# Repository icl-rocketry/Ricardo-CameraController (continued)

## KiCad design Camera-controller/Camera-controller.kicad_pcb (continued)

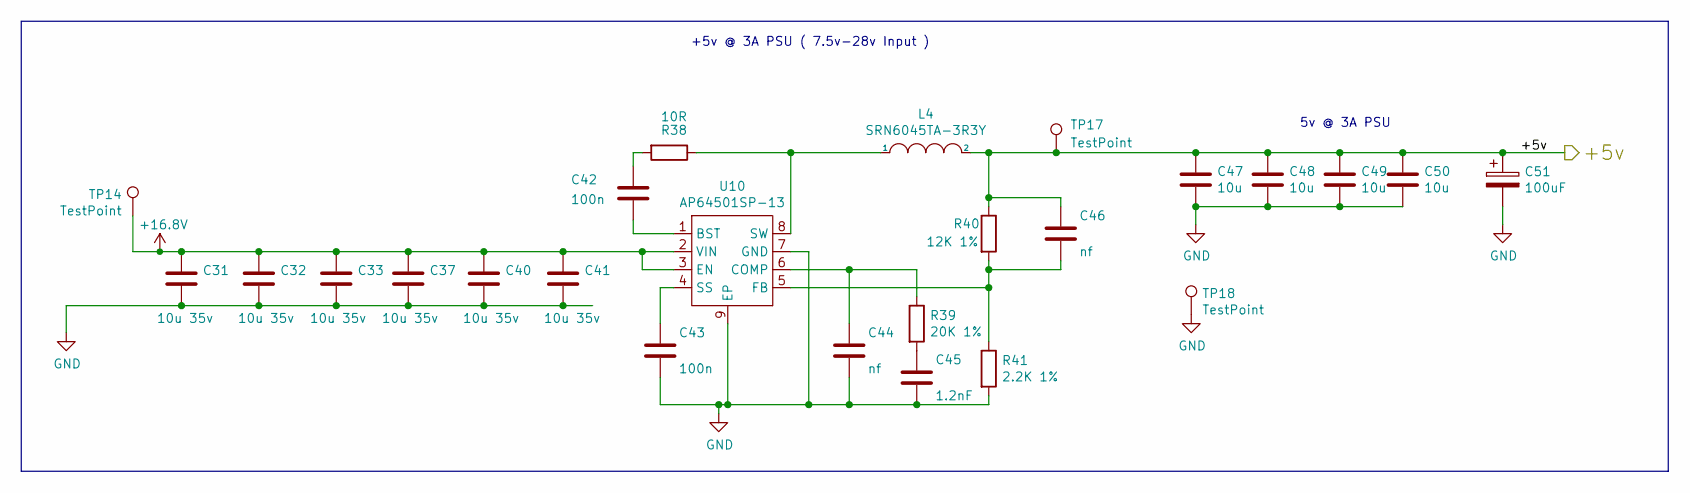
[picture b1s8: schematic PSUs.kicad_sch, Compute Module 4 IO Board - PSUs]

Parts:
C31, C32, C33, C37, C40, C41: 10u 35v; C_0805_2012Metric; Part Description 10uF 10% or 20% 35V Ceramic Capacitor X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
C42, C43: 100n; C_0402_1005Metric; Part Description 0.1uF 10% 16V Ceramic Capacitor X7R 040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
C44: nf; C_0402_1005Metric
C45: 1.2nF; C_0402_1005Metric; Part Description 1200pF 10% 10V Ceramic Capacitor X5R 04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
C46: nf; C_0402_1005Metric; Part Description 220 pF, 50 V, 0402 [1005 Metric], ± 5%,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
C47, C48, C49, C50: 10u; C_0805_2012Metric; Part Description 10uF 10% 10V Ceramic Capacitor X7R 0805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
C51: 100uF; CP_EIA-7343-31_Kemet-D; Part Description Capacitor, SP-Cap, 100u, 6.3V, 15mR ESR
L4: SRN6045TA-3R3Y; L_Bourns_SRN6045TA; Part Description 3.3µH Semi-Shielded Wirewound Inductor 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
R38: 10R; R_0402_1005Metric; Part Description Resistor 10R M1005 1% 63mW
R39: 20K 1%; R_0402_1005Metric; Part Description Resistor 20K M1005 1% 63mW
R40: 12K 1%; R_0402_1005Metric; Part Description Resistor 12K M1005 1% 63mW
R41: 2.2K 1%; R_0402_1005Metric; Part Description Resistor 2.2K M1005 1% 63mW
TP14, TP17, TP18: TestPoint; TestPoint_Pad_2.0x2.0mm
U10: AP64501SP-13; SOIC-8-1EP_3.9x4.9mm_P1.27mm_EP2.95x4.9mm_Mask2.71x3.4mm_Th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; Part Description Buck Switching Regulator IC Positive Ad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

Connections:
unnamed: C42.1, R38.2
unnamed: C45.1, R39.2
unnamed: C42.2, U10.1 (BST)
unnamed 188: C44.1, R39.1, U10.6 (COMP); also elsewhere on the board
unnamed: C43.1, U10.4 (SS)

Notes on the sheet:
5v @ 3A PSU
+5v @ 3A PSU ( 7.5v-28v Input )

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
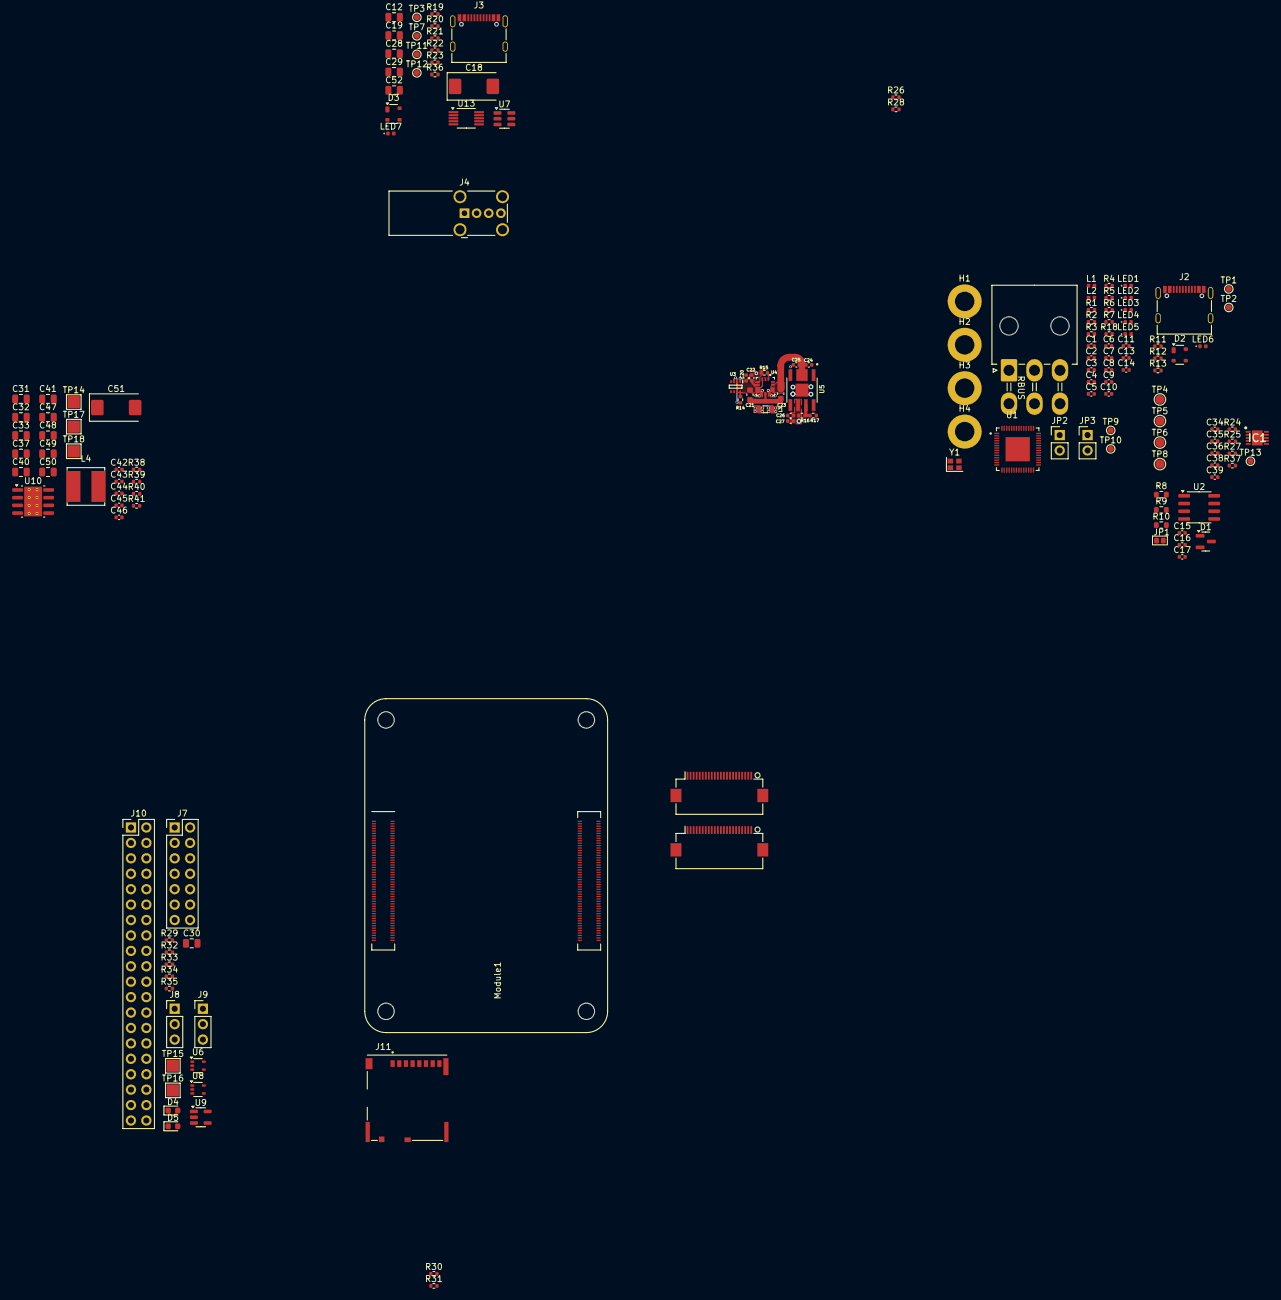
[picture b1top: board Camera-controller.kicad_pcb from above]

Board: 4 copper layers, 159 parts (0 on the bottom side), 141 nets.

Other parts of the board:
C15: 100nF; C_0402_1005Metric
C16: 10uF; C_0402_1005Metric
C17: 47nF; C_0402_1005Metric
D1: SM712_SOT23; SOT-23
JP1: TermJP; SmallerSolderJP
R8: 0; R_0603_1608Metric
R9, R10: 60; R_0603_1608Metric
U2: SN65HVD230; SOIC-8_3.9x4.9mm_P1.27mm

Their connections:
+3V3: C15.1, C16.1, U2.3 (VCC); also elsewhere on the board
/CAN+: D1.2 (A2), R9.1, U2.7 (CANH); also elsewhere on the board
/CAN-: D1.1 (A1), R10.2, U2.6 (CANL); also elsewhere on the board
/CAN-BUS/Vref: JP1.1 (A), U2.5 (Vref)
/CAN_RX: U2.4 (R); also elsewhere on the board
/CAN_TX: U2.1 (D); also elsewhere on the board
unnamed: C17.1, JP1.2 (B), R9.2, R10.1
unnamed: R8.1, U2.8 (Rs)

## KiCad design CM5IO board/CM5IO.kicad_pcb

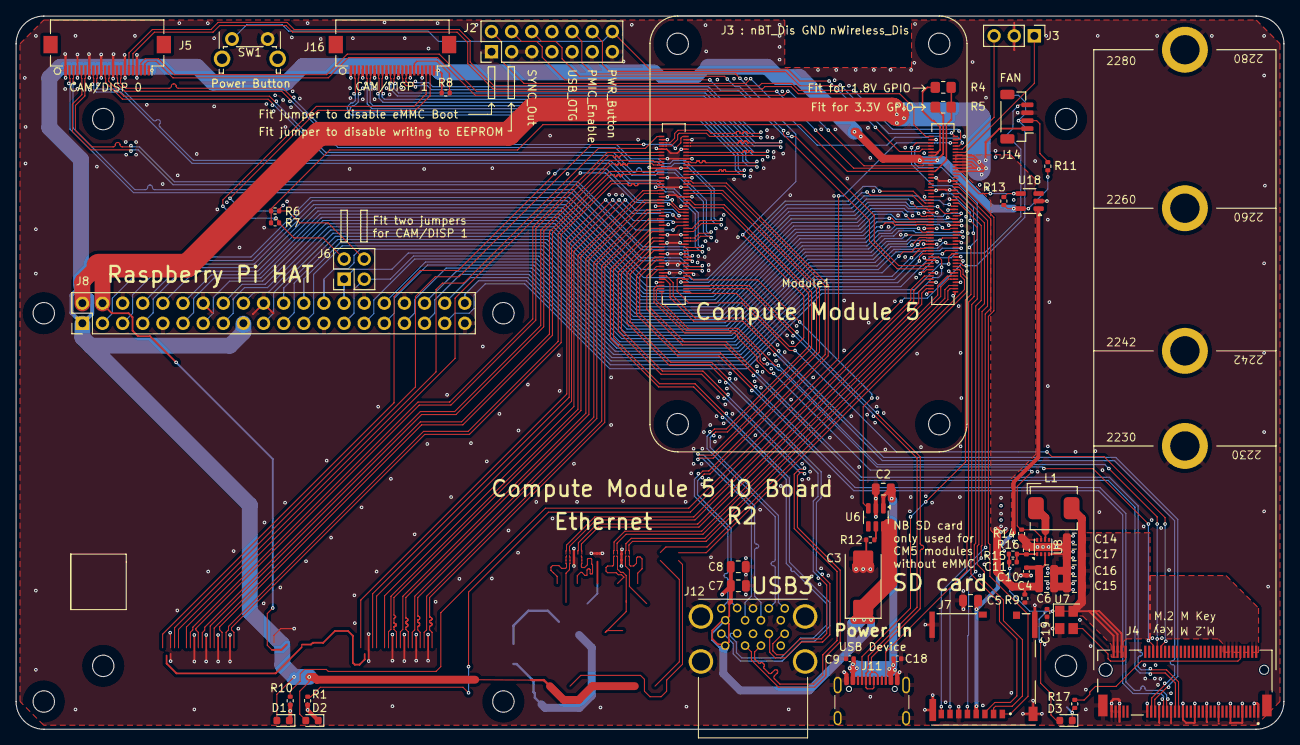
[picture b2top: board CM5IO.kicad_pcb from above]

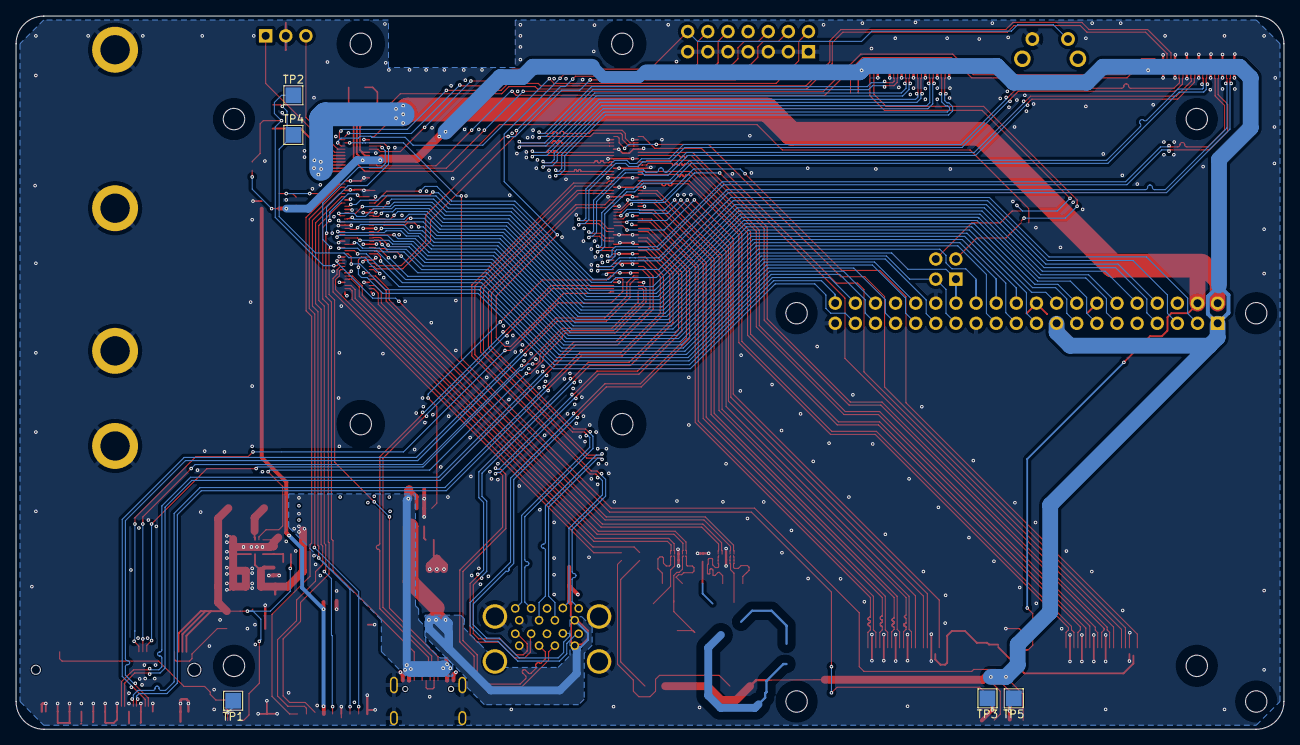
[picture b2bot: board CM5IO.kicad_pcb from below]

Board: 4 copper layers, 160.0 x 90.0 mm, 65 parts (5 on the bottom side), 118 nets.

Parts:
C2, C4, C5, C6, C7, C8, C14, C15, C16, C17: 10u; C_0805_2012Metric
C3: 100uF; CP_EIA-7343-31_Kemet-D
C9, C10, C18, C19: 100n; C_0402_1005Metric
C11: 4.7nF; C_0402_1005Metric
D1: LED Red; LED_0603_1608Metric
D2, D3: LED Green; LED_0603_1608Metric
H1, H2, H3, H4, H5, H6, H7, H8: MountingHole; MountingHole_2.7mm_M2.5_DIN965
J2: Conn_02x07_Odd_Even; PinHeader_2x07_P2.54mm_Vertical
J3: Conn_01x03; PinHeader_1x03_P2.54mm_Vertical
J4: Bus_M.2_Socket_M; M.2 M Key socket
J5, J16: Conn_01x22_Female; Hirose_FH12-22S-0.5SH_1x22-1MP_P0.50mm_Horizontal
J6: THD-02-R; PinHeader_2x02_P2.54mm_Vertical
J7: Micro_SD_Card_Det; SDCARD_MOLEX_503398-1892
J8: THD-20-R; PinHeader_2x20_P2.54mm_Vertical
J11: USB_C_Receptacle_USB2.0; USB_C_Receptacle_GCT_USB4105-xx-A_16P_TopMnt_Horizontal
J12: USB3_A; MTCONN_UBAF30-D2011
J14: JST_SHBM04B-SRSS-TB; JST_SH_BM04B-SRSS-TB_1x04-1MP_P1.00mm_Vertical
L1: 2.2uH; L_Bourns_SRP5030CC
Module1: ComputeModule5-CM5; Raspberry-Pi-5-Compute-Module
R1, R10, R17: 1k; R_0402_1005Metric
R4: nf; R_0805_2012Metric_Pad1.20x1.40mm_HandSolder
R5: 0R; R_0805_2012Metric_Pad1.20x1.40mm_HandSolder
R6, R7, R8, R9, R16: 2.2K 1%; R_0402_1005Metric
R11, R13, R15: 10K 1%; R_0402_1005Metric
R12: 15K 1%; R_0402_1005Metric
R14: 100K 1%; R_0402_1005Metric
SW1: Right angle Tact button; SW_Tactile_SPST_Angled_PTS645Vx58-2LFS
TP1, TP2, TP3, TP4, TP5: TestPoint; TestPoint_Pad_2.0x2.0mm
U6: AP22653W6; SOT-23-6
U7: ASEK-32.768KHZ-L-R-T; Crystal_SMD_3225-4Pin_3.2x2.5mm
U8: AP3441SHE-7B; DFN-8-1EP_2x2mm_P0.5mm_EP1.05x1.75mm
U18: RT9742GGJ5; SOT-23-5

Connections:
/+3.3v: D1.2 (A), D2.2 (A), J5.22, J8.1, J8.17, J16.22, Module1.84 (+3.3v_(Output)), Module1.86 (+3.3v_(Output)), R5.1, R8.1, R11.1, R13.1, U18.5 (IN)
/+5v: C4.1, C6.1, C9.1, C10.1, C18.1, J8.2, J8.4, J11.A4 (VBUS), J11.A9 (VBUS), J11.B4 (VBUS), J11.B9 (VBUS), J14.1, Module1.77 (+5v_(Input)), Module1.79 (+5v_(Input)), Module1.81 (+5v_(Input)), Module1.83 (+5v_(Input)), Module1.85 (+5v_(Input)), Module1.87 (+5v_(Input)), R9.1, U8.3 (VIN)
/CC1: J11.A5 (CC1), Module1.94 (CC1)
/CC2: J11.B5 (CC2), Module1.96 (CC2)
/CM5_GPIO ( Ethernet, GPIO, SDCARD)/+1.8v: Module1.88 (+1.8v_(Output)), Module1.90 (+1.8v_(Output)), R4.1
/CM5_GPIO ( Ethernet, GPIO, SDCARD)/BT_nDis: J3.3, Module1.91 (BT_nDisable)
/CM5_GPIO ( Ethernet, GPIO, SDCARD)/CAM_GPIO0: J5.17, Module1.97 (CAM_GPIO0)
/CM5_GPIO ( Ethernet, GPIO, SDCARD)/CAM_GPIO1: J5.18, Module1.100 (CAM_GPIO1)
/CM5_GPIO ( Ethernet, GPIO, SDCARD)/EEPROM_nWP: J2.4, Module1.20 (EEPROM_nWP)
/CM5_GPIO ( Ethernet, GPIO, SDCARD)/GPIO2: J8.3, Module1.58 (GPIO2)
/CM5_GPIO ( Ethernet, GPIO, SDCARD)/GPIO3: J8.5, Module1.56 (GPIO3)
/CM5_GPIO ( Ethernet, GPIO, SDCARD)/GPIO4: J8.7, Module1.54 (GPIO4)
/CM5_GPIO ( Ethernet, GPIO, SDCARD)/GPIO5: J8.29, Module1.34 (GPIO5)
/CM5_GPIO ( Ethernet, GPIO, SDCARD)/GPIO6: J8.31, Module1.30 (GPIO6)
/CM5_GPIO ( Ethernet, GPIO, SDCARD)/GPIO7: J8.26, Module1.37 (GPIO7)
/CM5_GPIO ( Ethernet, GPIO, SDCARD)/GPIO8: J8.24, Module1.39 (GPIO8)
/CM5_GPIO ( Ethernet, GPIO, SDCARD)/GPIO9: J8.21, Module1.40 (GPIO9)
/CM5_GPIO ( Ethernet, GPIO, SDCARD)/GPIO10: J8.19, Module1.44 (GPIO10)
/CM5_GPIO ( Ethernet, GPIO, SDCARD)/GPIO11: J8.23, Module1.38 (GPIO11)
/CM5_GPIO ( Ethernet, GPIO, SDCARD)/GPIO12: J8.32, Module1.31 (GPIO12)
/CM5_GPIO ( Ethernet, GPIO, SDCARD)/GPIO13: J8.33, Module1.28 (GPIO13)
/CM5_GPIO ( Ethernet, GPIO, SDCARD)/GPIO14: J8.8, Module1.55 (GPIO14)
/CM5_GPIO ( Ethernet, GPIO, SDCARD)/GPIO15: J8.10, Module1.51 (GPIO15)
/CM5_GPIO ( Ethernet, GPIO, SDCARD)/GPIO16: J8.36, Module1.29 (GPIO16)
/CM5_GPIO ( Ethernet, GPIO, SDCARD)/GPIO17: J8.11, Module1.50 (GPIO17)
/CM5_GPIO ( Ethernet, GPIO, SDCARD)/GPIO18: J8.12, Module1.49 (GPIO18)
/CM5_GPIO ( Ethernet, GPIO, SDCARD)/GPIO19: J8.35, Module1.26 (GPIO19)
/CM5_GPIO ( Ethernet, GPIO, SDCARD)/GPIO20: J8.38, Module1.27 (GPIO20)
/CM5_GPIO ( Ethernet, GPIO, SDCARD)/GPIO21: J8.40, Module1.25 (GPIO21)
/CM5_GPIO ( Ethernet, GPIO, SDCARD)/GPIO22: J8.15, Module1.46 (GPIO22)
/CM5_GPIO ( Ethernet, GPIO, SDCARD)/GPIO23: J8.16, Module1.47 (GPIO23)
/CM5_GPIO ( Ethernet, GPIO, SDCARD)/GPIO24: J8.18, Module1.45 (GPIO24)
/CM5_GPIO ( Ethernet, GPIO, SDCARD)/GPIO25: J8.22, Module1.41 (GPIO25)
/CM5_GPIO ( Ethernet, GPIO, SDCARD)/GPIO26: J8.37, Module1.24 (GPIO26)
/CM5_GPIO ( Ethernet, GPIO, SDCARD)/GPIO27: J8.13, Module1.48 (GPIO27)
/CM5_GPIO ( Ethernet, GPIO, SDCARD)/GPIO_VREF: Module1.78 (GPIO_VREF(1.8v/3.3v_Input)), R4.2, R5.2, R6.1, R7.1
/CM5_GPIO ( Ethernet, GPIO, SDCARD)/ID_SC: J6.1, J8.28, Module1.35 (ID_SC)
/CM5_GPIO ( Ethernet, GPIO, SDCARD)/ID_SD: J6.3, J8.27, Module1.36 (ID_SD)
/CM5_GPIO ( Ethernet, GPIO, SDCARD)/PMIC_ENABLE: J2.12, Module1.99 (PMIC_ENABLE)
/CM5_GPIO ( Ethernet, GPIO, SDCARD)/PWM: J14.2, Module1.19 (FAN_PWM), R11.2, TP2.1
/CM5_GPIO ( Ethernet, GPIO, SDCARD)/PWR_BUT: J2.14, Module1.92 (PWR_BUT), SW1.1
/CM5_GPIO ( Ethernet, GPIO, SDCARD)/SD_CLK: J7.5 (CLK), Module1.57 (SD_CLK)
/CM5_GPIO ( Ethernet, GPIO, SDCARD)/SD_CMD: J7.3 (CMD), Module1.62 (SD_CMD)
/CM5_GPIO ( Ethernet, GPIO, SDCARD)/SD_DAT0: J7.7 (DAT0), Module1.63 (SD_DAT0)
/CM5_GPIO ( Ethernet, GPIO, SDCARD)/SD_DAT1: J7.8 (DAT1), Module1.67 (SD_DAT1)
/CM5_GPIO ( Ethernet, GPIO, SDCARD)/SD_DAT2: J7.1 (DAT2), Module1.69 (SD_DAT2)
/CM5_GPIO ( Ethernet, GPIO, SDCARD)/SD_DAT3: J7.2 (DAT3/CD), Module1.61 (SD_DAT3)
/CM5_GPIO ( Ethernet, GPIO, SDCARD)/SD_PWR: C5.1, J7.4 (VDD), U18.1 (OUT)
/CM5_GPIO ( Ethernet, GPIO, SDCARD)/SD_PWR_ON: Module1.75 (SD_PWR_ON), R13.2, U18.4 (EN)
/CM5_GPIO ( Ethernet, GPIO, SDCARD)/TACHO: J14.4, Module1.16 (FAN_TACHO), TP4.1
/CM5_GPIO ( Ethernet, GPIO, SDCARD)/USBOTG: J2.10, Module1.101 (USB_OTG_ID)
/CM5_GPIO ( Ethernet, GPIO, SDCARD)/WL_nDis: J3.1, Module1.89 (WiFi_nDisable)
/CM5_GPIO ( Ethernet, GPIO, SDCARD)/nPWR_LED: Module1.95 (LED_nPWR), R10.2
/CM5_GPIO ( Ethernet, GPIO, SDCARD)/nRPIBOOT: J2.2, Module1.93 (nRPIBOOT)
/CM5_HighSpeed/+5v: C2.1, U6.1 (IN)
/CM5_HighSpeed/DPHY0_C_N: J5.8, Module1.127 (MIPI0_C_N)
/CM5_HighSpeed/DPHY0_C_P: J5.9, Module1.129 (MIPI0_C_P)
/CM5_HighSpeed/DPHY0_D0_N: J5.2, Module1.115 (MIPI0_D0_N)
/CM5_HighSpeed/DPHY0_D0_P: J5.3, Module1.117 (MIPI0_D0_P)
/CM5_HighSpeed/DPHY0_D1_N: J5.5, Module1.121 (MIPI0_D1_N)
/CM5_HighSpeed/DPHY0_D1_P: J5.6, Module1.123 (MIPI0_D1_P)
/CM5_HighSpeed/DPHY0_D2_N: J5.11, Module1.133 (MIPI0_D2_N)
/CM5_HighSpeed/DPHY0_D2_P: J5.12, Module1.135 (MIPI0_D2_P)
/CM5_HighSpeed/DPHY0_D3_N: J5.14, Module1.139 (MIPI0_D3_N)
/CM5_HighSpeed/DPHY0_D3_P: J5.15, Module1.141 (MIPI0_D3_P)
/CM5_HighSpeed/DPHY1_C_N: J16.8, Module1.187 (MIPI1_C_N)
/CM5_HighSpeed/DPHY1_C_P: J16.9, Module1.189 (MIPI1_C_P)
/CM5_HighSpeed/DPHY1_D0_N: J16.2, Module1.175 (MIPI1_D0_N)
/CM5_HighSpeed/DPHY1_D0_P: J16.3, Module1.177 (MIPI1_D0_P)
/CM5_HighSpeed/DPHY1_D1_N: J16.5, Module1.181 (MIPI1_D1_N)
/CM5_HighSpeed/DPHY1_D1_P: J16.6, Module1.183 (MIPI1_D1_P)
/CM5_HighSpeed/DPHY1_D2_N: J16.11, Module1.193 (MIPI1_D2_N)
/CM5_HighSpeed/DPHY1_D2_P: J16.12, Module1.195 (MIPI1_D2_P)
/CM5_HighSpeed/DPHY1_D3_N: J16.14, Module1.194 (MIPI1_D3_N)
/CM5_HighSpeed/DPHY1_D3_P: J16.15, Module1.196 (MIPI1_D3_P)
/CM5_HighSpeed/PCIE_CLK_N: J4.53 (REFCLKn), Module1.112 (PCIe_CLK_N)
/CM5_HighSpeed/PCIE_CLK_P: J4.55 (REFCLKp), Module1.110 (PCIe_CLK_P)
/CM5_HighSpeed/PCIE_PWR_EN: Module1.106 (PCIE_PWR_EN), R14.1, U8.7 (EN)
/CM5_HighSpeed/PCIE_RX_N: J4.43 (PETp0), Module1.118 (PCIe_RX_N)
/CM5_HighSpeed/PCIE_RX_P: J4.41 (PETn0), Module1.116 (PCIe_RX_P)
/CM5_HighSpeed/PCIE_TX_N: J4.49 (PERp0), Module1.124 (PCIe_TX_N)
/CM5_HighSpeed/PCIE_TX_P: J4.47 (PERn0), Module1.122 (PCIe_TX_P)
/CM5_HighSpeed/PCIE_nCLKREQ: J4.52 (~CLKREQ), Module1.102 (PCIe_nCLKREQ)
/CM5_HighSpeed/PCIE_nRST: J4.50 (~PERST), Module1.109 (PCIe_nRST)
/CM5_HighSpeed/PCIE_nWAKE: J4.54 (~PEWAKE), Module1.104 (PCIE_nWAKE)
/CM5_HighSpeed/SCL0: J5.20, Module1.80 (SCL0)
/CM5_HighSpeed/SCL1: J6.2, J16.20, R7.2
/CM5_HighSpeed/SDA0: J5.21, Module1.82 (SDA0)
/CM5_HighSpeed/SDA1: J6.4, J16.21, R6.2
/CM5_HighSpeed/USB3-0-D_N: J12.A2 (D-), Module1.136 (USB3-0-D_N)
/CM5_HighSpeed/USB3-0-D_P: J12.A3 (D+), Module1.134 (USB3-0-D_P)
/CM5_HighSpeed/USB3-0-RX_N: J12.A6 (SSRX+), Module1.128 (USB3-0-RX_N)
/CM5_HighSpeed/USB3-0-RX_P: J12.A5 (SSRX-), Module1.130 (USB3-0-RX_P)
/CM5_HighSpeed/USB3-0-TX_N: J12.A9 (SSTX+), Module1.140 (USB3-0-TX_N)
/CM5_HighSpeed/USB3-0-TX_P: J12.A8 (SSTX-), Module1.142 (USB3-0-TX_P)
/CM5_HighSpeed/USB3-1-D_N: J12.B2 (D-), Module1.165 (USB3-1-D_N)
/CM5_HighSpeed/USB3-1-D_P: J12.B3 (D+), Module1.163 (USB3-1-D_P)
/CM5_HighSpeed/USB3-1-RX_N: J12.B6 (SSRX+), Module1.157 (USB3-1-RX_N)
/CM5_HighSpeed/USB3-1-RX_P: J12.B5 (SSRX-), Module1.159 (USB3-1-RX_P)
/CM5_HighSpeed/USB3-1-TX_N: J12.B9 (SSTX+), Module1.169 (USB3-1-TX_N)
/CM5_HighSpeed/USB3-1-TX_P: J12.B8 (SSTX-), Module1.171 (USB3-1-TX_P)
/CM5_HighSpeed/VBUS: C3.1, C7.1, C8.1, J12.A1 (VBUS), J12.B1 (VBUS), U6.6 (OUT)
/CM5_HighSpeed/VBUS_EN: Module1.111 (VBUS_EN), U6.3 (EN)
/PCIe-M2/FB: C11.2, R15.2, R16.1, U8.1 (FB)
/PCIe-M2/M2_3v3: C11.1, C14.1, C15.1, C16.1, C17.1, C19.1, D3.2 (A), J4.2 (3.3V), J4.4 (3.3V), J4.12 (3.3V), J4.14 (3.3V), J4.16 (3.3V), J4.18 (3.3V), J4.70 (3.3V), J4.72 (3.3V), J4.74 (3.3V), L1.2, R15.1, U7.1 (EN), U7.4 (VDD)
/USB2_N: J11.A7 (D-), J11.B7 (D-), Module1.103 (USB2_N)
/USB2_P: J11.A6 (D+), J11.B6 (D+), Module1.105 (USB2_P)
GND: C2.2, C3.2, C4.2, C5.2, C6.2, C7.2, C8.2, C9.2, C10.2, C14.2, C15.2, C16.2, C17.2, C18.2, C19.2, J2.1, J2.3, J2.5, J2.7, J2.9, J2.11, J2.13, J3.2, J4.1 (GND), J4.3 (GND), J4.9 (GND), J4.15 (GND), J4.21 (GND), J4.27 (GND), J4.33 (GND), J4.39 (GND), J4.45 (GND), J4.51 (GND), J4.57 (GND), J4.71 (GND), J4.73 (GND), J4.75 (GND), J4.M1 (GND2230), J4.M2 (GND2242), J4.M3 (GND2260), J4.M4 (GND2280), J4.S1, J4.S2, J5.1, J5.4, J5.7, J5.10, J5.13, J5.16, J5.19, J7.6 (VSS), J7.11 (SHIELD), J8.6, J8.9, J8.14, J8.20, J8.25, J8.30, J8.34, J8.39, J11.A1 (GND), J11.A12 (GND), J11.B1 (GND), J11.B12 (GND), J11.S1 (SHIELD), J12.10 (SHIELD), J12.A4 (GND), J12.A7 (DRAIN), J12.B4 (GND), J12.B7 (DRAIN), J14.3, J16.1, J16.4, J16.7, J16.10, J16.13, J16.16, J16.19, Module1.8 (GND), Module1.14 (GND), Module1.22 (GND), Module1.23 (GND), Module1.32 (GND), Module1.33 (GND), Module1.42 (GND), Module1.43 (GND), Module1.52 (GND), Module1.53 (GND), Module1.59 (GND), Module1.60 (GND), Module1.65 (GND), Module1.66 (GND), Module1.71 (GND), Module1.74 (GND), Module1.98 (GND), Module1.107 (GND), Module1.113 (GND), Module1.119 (GND), Module1.125 (GND), Module1.131 (GND), Module1.137 (GND), Module1.155 (GND), Module1.161 (GND), Module1.167 (GND), Module1.173 (GND), Module1.179 (GND), Module1.185 (GND), Module1.191 (GND), Module1.192 (GND), Module1.197 (GND), Module1.198 (GND), R9.2, R12.2, R14.2, R16.2, SW1.2, U6.2 (GND), U7.2 (GND), U8.4 (PGND), U8.8 (SGND), U8.9 (PAD), U18.2 (GND)
unnamed: D1.1 (K), R10.1, TP5.1
unnamed: D2.1 (K), R1.1, TP3.1
unnamed: D3.1 (K), R17.1, TP1.1
unnamed: J4.10 (DAS/~DSS/~LED1), R17.2
unnamed: J4.68 (SUSCLK), U7.3 (Out)
unnamed: J16.17, R8.2
unnamed: Module1.21 (LED_nACT), R1.2
unnamed: Module1.108 (GND), Module1.114 (GND), Module1.120 (GND), Module1.126 (GND), Module1.132 (GND), Module1.138 (GND), Module1.144 (GND)
unnamed: R12.1, U6.5 (ILIM)
unnamed: L1.1, U8.6 (LX)

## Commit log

2026-02-03 KiCad project made
2026-02-03 Template cloned
2026-02-03 CM5 schematic drawn [KiCad]
2026-02-17 Added CM5 reference board file
2026-02-24 Moved Camera-Controller-CM5IO to main folder
2026-02-24 Attempted to delete HDMI from sch. #1
2026-02-24 Moved CM5IO folder; Removed Ethernet, Battery (successfully?)
2026-02-24 Copied Ricardo template on CM5IO board
    There's not enough space!!
2026-02-24 Duplicated additional USB-C in sch.
    How to change pin label on CM5?
2026-03-03 Moved Ricardo to hierarchical sheet in main sch.
2026-03-03 Added "Buck Boost" hierarchical sheet; Deleted two USB-C ports
2026-03-10 Blocked off vbat
    still need to block off ethernet
2026-03-14 Began design of RBUS(4-5V)-to-CM5(5V) boost
    R1, R2, R3 selected; Explained difference between GNDA and GND.
2026-03-17 Continued boost design
    R4, C1, C2, C3 selected
    R4, L1 unsure
    COMP, EN yet to be finished.
2026-03-17 C3 GND -> GNDA
    small mistake
2026-06-11 EN L1 completed
    R_EN set to 800k (typ) (could be 10k) | L1 set to 2.2uH (744311220 Wurth); imported to iclr-hw
2026-06-16 Edited I/O port names for consistency
    e.g. FSW_IN & FSW_OUT -> FSW_IO
2026-06-16 EN changed & finalised
    Added MOSFET; using potential divider (i.e. R7//R8) EN switch is at 1.65V which is >1.2V from the data sheet. Added C7 to avoid voltage spikes.
2026-06-16 COMP completed
    η ≈ 85% | D = 0.45 | R_O = 1.67Ω | f_RHPZ = 36546 Hz | f_C ≈ 7 kHz | R5 = 6.2kΩ | C5 = 6 nF | R_ESR ≈ 0.05Ω | C6 = 360 pF
2026-06-25 feat: CM4 migration
    Massive changes moving to use a CM4 for rubyfpv support. Power system sorted for ESP and PI, but not hawkeye v5s
